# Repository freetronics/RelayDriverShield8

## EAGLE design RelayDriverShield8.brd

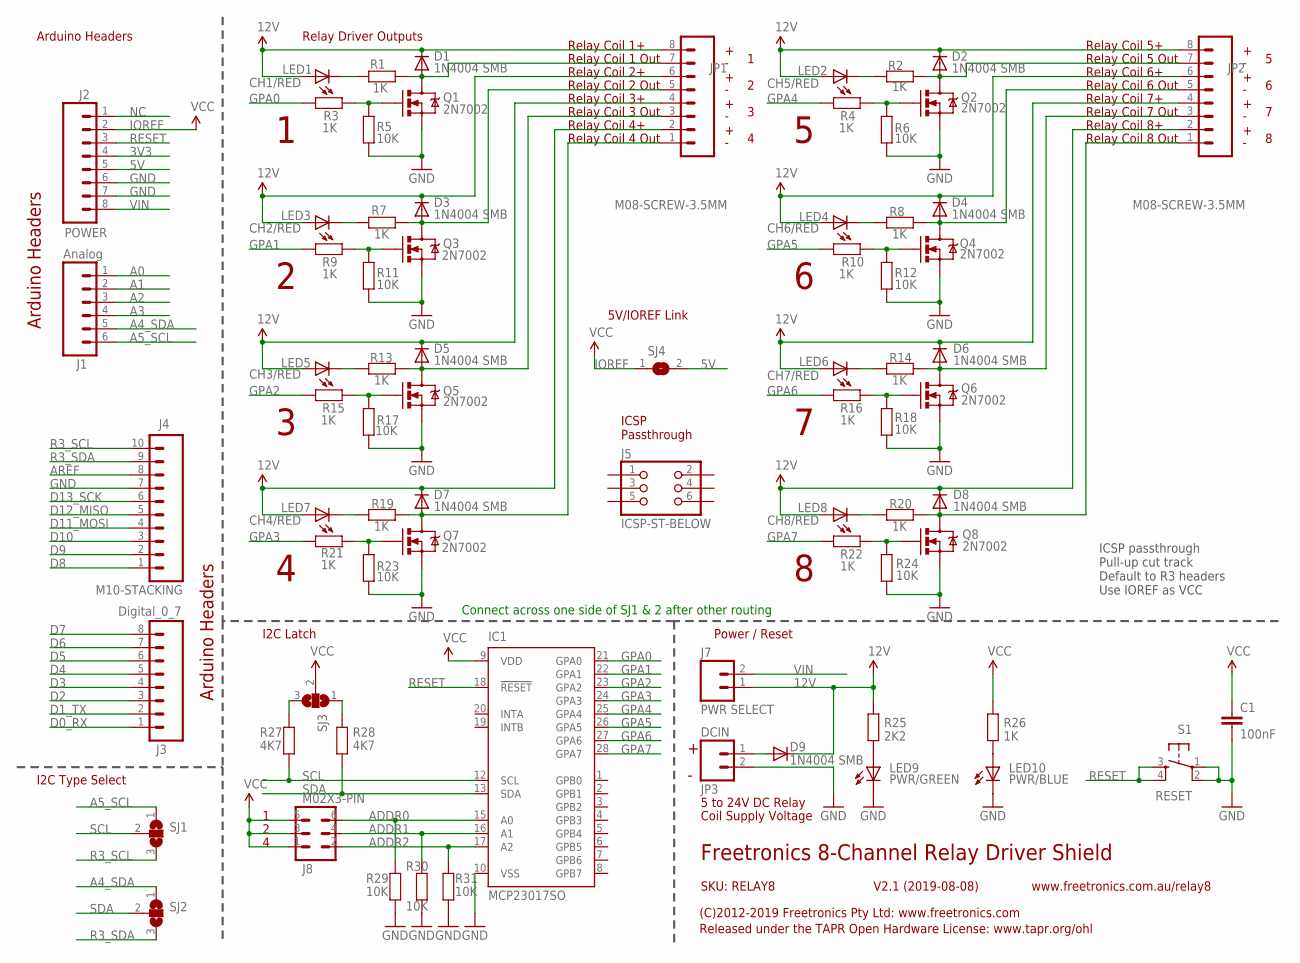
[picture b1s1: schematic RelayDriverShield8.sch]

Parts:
C1: 100nF; C0603
D1, D2, D3, D4, D5, D6, D7, D8, D9: 1N4004 SMB; SMA-DIODE
IC1: MCP23017SO; SO28W
J1: Analog; 1X06-ST
J2: POWER; 1X08-ST
J3: Digital_0_7; 1X08-ST
J4: M10-STACKING; 1X10-ST
J5: ICSP-ST-BELOW; 2X03-ICSP-ST-BELOW
J7: PWR SELECT; 1X02-P
J8: M02X3-PIN; 2X03-P
JP1, JP2: M08-SCREW-3.5MM; SCREWTERMINAL_3.5MM_8
JP3: DCIN; SCREWTERMINAL-3.5MM-2
LED1: CH1/RED; LED-0603
LED2: CH5/RED; LED-0603
LED3: CH2/RED; LED-0603
LED4: CH6/RED; LED-0603
LED5: CH3/RED; LED-0603
LED6: CH7/RED; LED-0603
LED7: CH4/RED; LED-0603
LED8: CH8/RED; LED-0603
LED9: PWR/GREEN; LED-0603
LED10: PWR/BLUE; LED-0603
Q1, Q2, Q3, Q4, Q5, Q6, Q7, Q8: 2N7002; SOT23-3
R1, R2, R3, R4, R7, R8, R9, R10, R13, R14, R15, R16, R19, R20, R21, R22, R26: 1K; R0603
R5, R6, R11, R12, R17, R18, R23, R24, R29, R30, R31: 10K; R0603
R25: 2K2; R0603
R27, R28: 4K7; R0603
S1: RESET; TACTILE_SMT-6MM
SJ1, SJ2, SJ3: SJ2W; SJ_2
SJ4: SJN; SJ

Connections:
3V3: J2.4
5V: J2.5, SJ4.2
12V: D1.C, D2.C, D3.C, D4.C, D5.C, D6.C, D7.C, D8.C, D9.C, J7.1, JP1.2, JP1.4, JP1.6, JP1.8, JP2.2, JP2.4, JP2.6, JP2.8, LED1.A, LED2.A, LED3.A, LED4.A, LED5.A, LED6.A, LED7.A, LED8.A, R25.2
A0: J1.1
A1: J1.2
A2: J1.3
A3: J1.4
A4_SDA: J1.5, SJ2.1
A5_SCL: J1.6, SJ1.1
ADDR0: IC1.15 (A0), J8.6, R29.2
ADDR1: IC1.16 (A1), J8.4, R30.2
ADDR2: IC1.17 (A2), J8.2, R31.2
AREF: J4.8
D0_RX: J3.1
D1_TX: J3.2
D2: J3.3
D3: J3.4
D4: J3.5
D5: J3.6
D6: J3.7
D7: J3.8
D8: J4.1
D9: J4.2
D10: J4.3
D11_MOSI: J4.4
D12_MISO: J4.5
D13_SCK: J4.6
GND: C1.2, IC1.10 (VSS), J2.6, J2.7, J4.7, JP3.2, LED9.C, LED10.C, Q1.2 (S), Q2.2 (S), Q3.2 (S), Q4.2 (S), Q5.2 (S), Q6.2 (S), Q7.2 (S), Q8.2 (S), R5.1, R6.1, R11.1, R12.1, R17.1, R18.1, R23.1, R24.1, R29.1, R30.1, R31.1, S1.1, S1.2
GPA0: IC1.21 (GPA0), R3.2
GPA1: IC1.22 (GPA1), R9.2
GPA2: IC1.23 (GPA2), R15.2
GPA3: IC1.24 (GPA3), R21.2
GPA4: IC1.25 (GPA4), R4.2
GPA5: IC1.26 (GPA5), R10.2
GPA6: IC1.27 (GPA6), R16.2
GPA7: IC1.28 (GPA7), R22.2
IOREF: C1.1, IC1.9 (VDD), J2.2, J8.1, J8.3, J8.5, R26.2, SJ3.2, SJ4.1
unnamed: Q1.1 (G), R3.1, R5.2
unnamed: D3.A, JP1.5, Q3.3 (D), R7.2
unnamed: LED9.A, R25.1
unnamed: D1.A, JP1.7, Q1.3 (D), R1.2
unnamed: Q3.1 (G), R9.1, R11.2
unnamed: D5.A, JP1.3, Q5.3 (D), R13.2
unnamed: Q5.1 (G), R15.1, R17.2
unnamed: D7.A, JP1.1, Q7.3 (D), R19.2
unnamed: Q7.1 (G), R21.1, R23.2
unnamed: D2.A, JP2.7, Q2.3 (D), R2.2
unnamed: Q2.1 (G), R4.1, R6.2
unnamed: D4.A, JP2.5, Q4.3 (D), R8.2
unnamed: Q4.1 (G), R10.1, R12.2
unnamed: D6.A, JP2.3, Q6.3 (D), R14.2
unnamed: Q6.1 (G), R16.1, R18.2
unnamed: D8.A, JP2.1, Q8.3 (D), R20.2
unnamed: Q8.1 (G), R22.1, R24.2
unnamed: LED3.C, R7.1
unnamed: LED7.C, R19.1
unnamed: LED5.C, R13.1
unnamed: LED1.C, R1.1
unnamed: LED2.C, R2.1
unnamed: LED4.C, R8.1
unnamed: LED6.C, R14.1
unnamed: LED8.C, R20.1
unnamed: D9.A, JP3.1
unnamed: R27.2, SJ3.3
unnamed: R28.2, SJ3.1
unnamed: LED10.A, R26.1
NC: J2.1
R3_SCL: J4.10, SJ1.3
R3_SDA: J4.9, SJ2.3
RESET: IC1.18 (!RESET), J2.3, S1.3, S1.4
SCL: IC1.12 (SCL), R27.1, SJ1.2
SDA: IC1.13 (SDA), R28.1, SJ2.2
VIN: J2.8, J7.2

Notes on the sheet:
Freetronics 8-Channel Relay Driver Shield
V2.1 (2019-08-08)
SKU: RELAY8
Arduino Headers
Power / Reset
I2C Latch
(C)2012-2019 Freetronics Pty Ltd: www.freetronics.com
Released under the TAPR Open Hardware License: www.tapr.org/ohl
www.freetronics.com.au/relay8
I2C Type Select
Relay Coil 1 Out
Relay Coil 1+
Relay Coil 2+
Relay Coil 3+
Relay Coil 4+
Relay Coil 4 Out
Relay Coil 3 Out
Relay Coil 2 Out
Relay Coil 8 Out
Relay Coil 8+
Relay Coil 5+
Relay Coil 5 Out
Relay Coil 6+
Relay Coil 6 Out
Relay Coil 7+
Relay Coil 7 Out
5 to 24V DC Relay
Coil Supply Voltage
Relay Driver Outputs
Connect across one side of SJ1 & 2 after other routing
ICSP passthrough Pull-up cut track Default to R3 headers Use IOREF as VCC
ICSP Passthrough
5V/IOREF Link

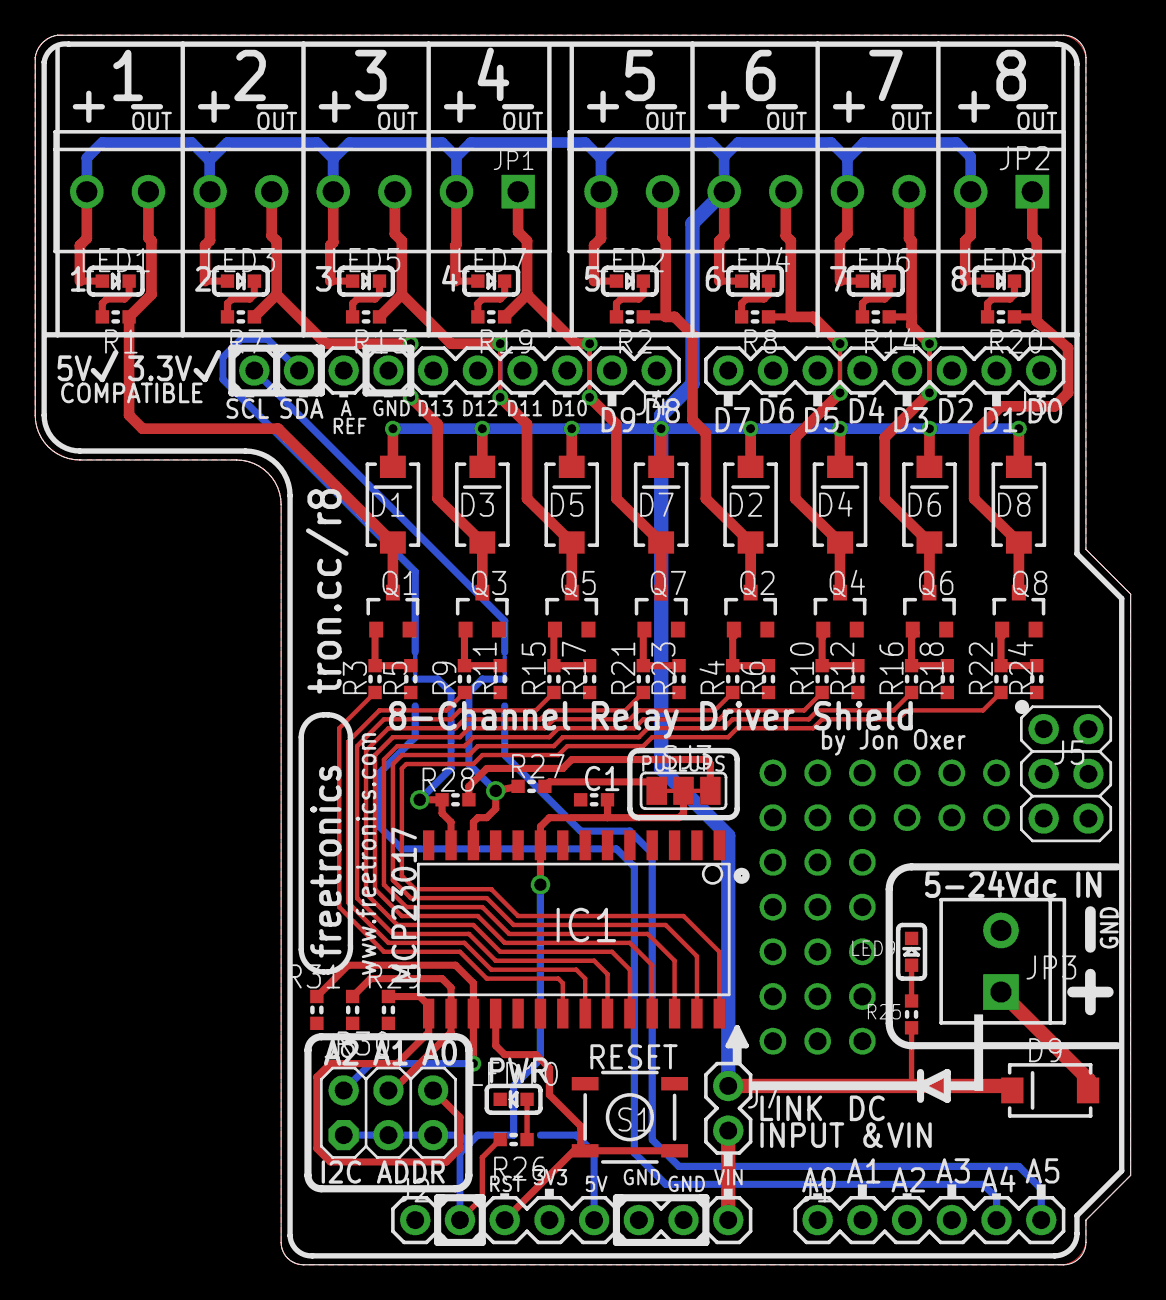
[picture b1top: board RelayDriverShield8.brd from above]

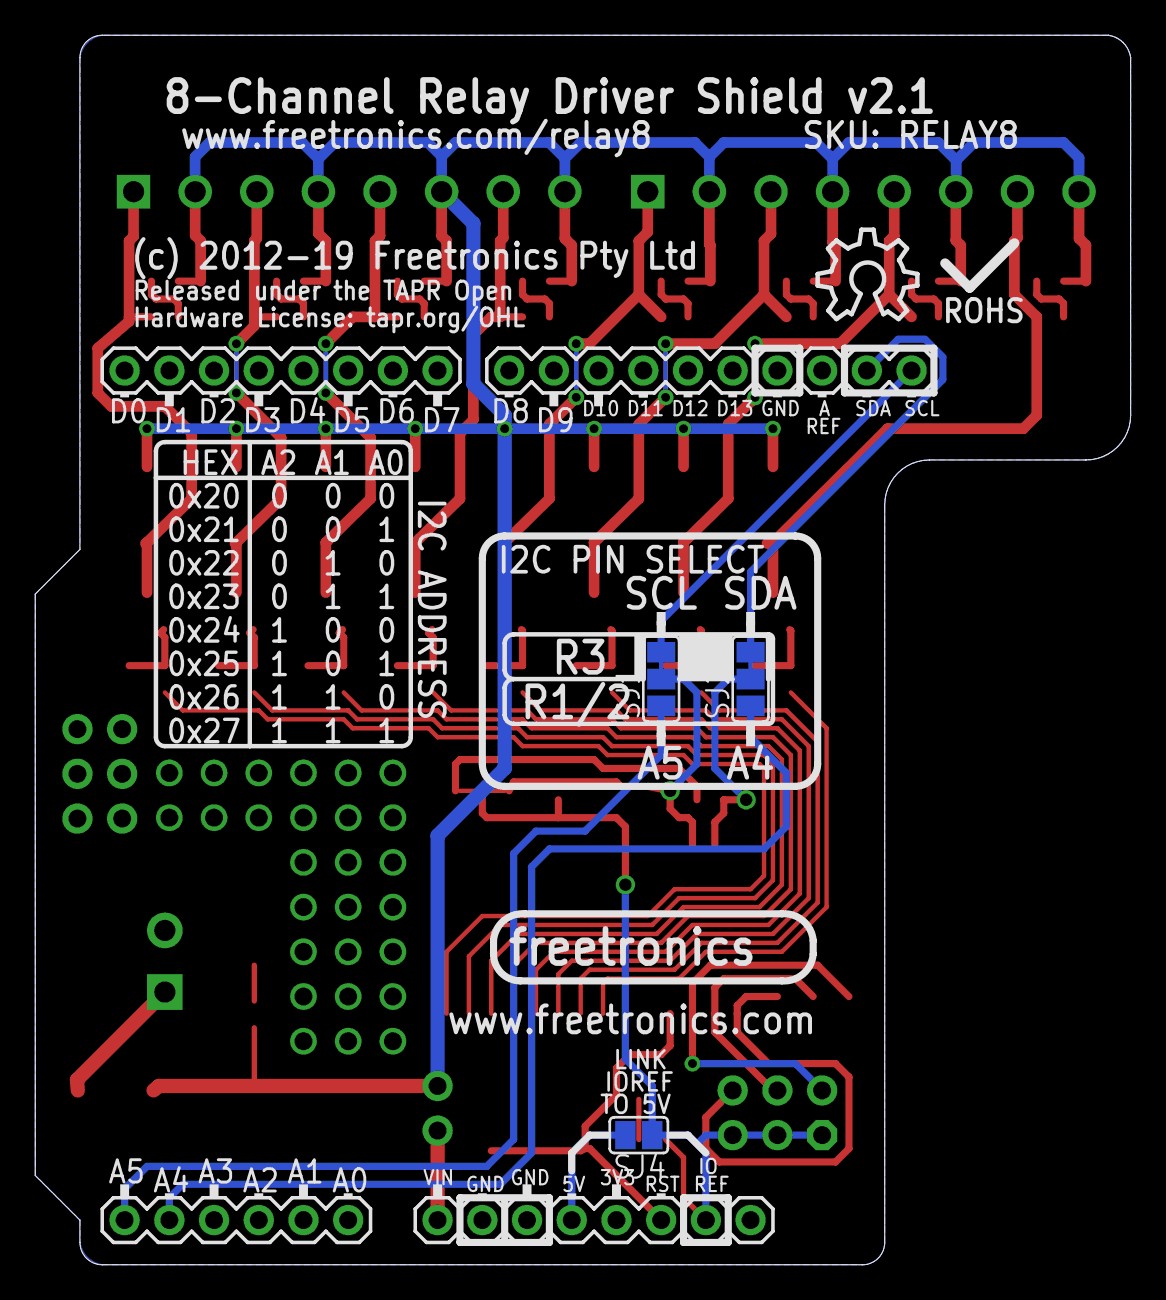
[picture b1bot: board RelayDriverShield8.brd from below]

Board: 2 copper layers, 62.2 x 69.8 mm, 76 parts (4 on the bottom side), 52 nets.

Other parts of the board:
U$6: OSHW_10X200_NOTEXT

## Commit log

2012-02-14 Initial project import
2012-02-28 Layout and schematic fixes, getting closer to 1.0
2012-03-25 Updated overlay, schematic, and license for v1.0 release
2012-05-01 Experimenting with reshaping the board for larger screw terminals
2012-05-02 Experiment with header version selection jumpers
2012-05-03 Routing
2012-05-05 Changed restring, improved clearances and routing, replaced pair of 1x3 headers with 2x3
2012-05-07 Start of clarifying schematic; replaced Zeners with 1N4004
2012-05-10 Schematic, routing, and overlay improvements
2012-05-11 Improvements to overlay and schematic
2012-05-11 Minor adjustments for production
2012-05-12 PDF schematic done
2014-06-03 Default pin selection to R3 headers instead of A4/A5 ICSP header for pass-through Cut-track jumpers to isolate I2C pullups Use IOREF as VCC for compatibility with both 3.3V and 5V hosts Relocate Pwr 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
2014-06-03 Updated SKU and schematic PDF
2014-06-30 Added solder jumper to link IOREF and 5V
2014-06-30 Improved value label positions
2019-04-24 Improved designator clarity
2019-08-08 Replaced parts using SuperHouse library to add 3D models
2021-03-11 Added PDF of schematic.

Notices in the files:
RelayDriverShield8.brd:
(c) 2012-19 Freetronics Pty Ltd
Hardware License: tapr.org/OHL
